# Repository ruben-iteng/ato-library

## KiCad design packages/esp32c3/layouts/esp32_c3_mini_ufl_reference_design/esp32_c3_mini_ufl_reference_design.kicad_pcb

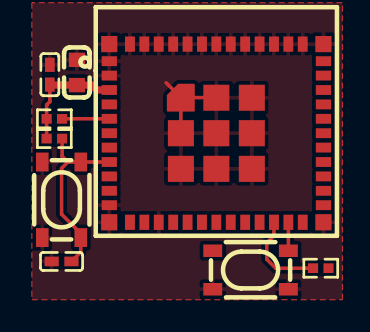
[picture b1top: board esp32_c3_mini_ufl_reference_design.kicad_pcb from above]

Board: 2 copper layers, 9 parts (0 on the bottom side), 6 nets.

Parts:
C1: 22µF ±20% 6.3V X5R; C0603-bd72f6
C2: 100nF ±10% 16V X7R; C0402-b3ef17
C3: 1µF ±10% 25V X5R; C0402-b3ef17
R1, R2, R3: 10kΩ ±1% 62.5mW; R0402-56259e
U1, U3: KEY-SMD_4P-L4.2-W3.2-P2.20-LS4.6
U2: WIFIM-SMD_ESP32-C3-MINI-MINI-1U-1cb675

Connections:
gnd: C1.2, C2.2, C3.2, U1.1, U1.2, U2.1, U2.2, U2.11, U2.14, U2.36, U2.37, U2.38, U2.39, U2.40, U2.41, U2.42, U2.43, U2.44, U2.45, U2.46, U2.47, U2.48, U2.49, U2.50, U2.51, U2.52, U2.53, U2.54, U2.55, U2.56, U2.57, U2.58, U2.59, U2.60, U2.61, U3.1, U3.2
hv: C1.1, C2.1, R1.2, R2.2, R3.1, U2.3
line: R1.1, U2.5
line-1: R2.1, U2.22
output: U1.3, U1.4, U2.23
output-1: C3.1, R3.2, U2.8, U3.3, U3.4

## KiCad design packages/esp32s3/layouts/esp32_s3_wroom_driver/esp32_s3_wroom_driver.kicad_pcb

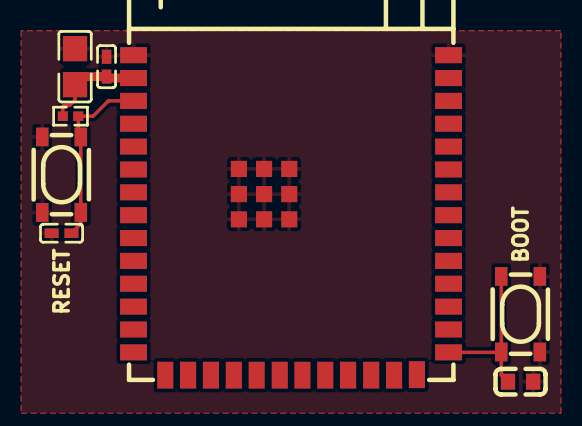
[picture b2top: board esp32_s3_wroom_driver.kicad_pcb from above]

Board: 2 copper layers, 8 parts (0 on the bottom side), 4 nets.

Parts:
C1: 100nF ±10% 50V X7R; C0805
C2, C3: 100nF ±10% 16V X7R; C0402
C4: 100nF ±10% 50V X7R; C0603
R1: 10kΩ ±1% 62.5mW; R0402
U1, U3: KEY-SMD_4P-L4.2-W3.2-P2.20-LS4.6
U2: WIRELM-SMD_ESP32-S3-WROOM-1

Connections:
gnd: C1.2, C2.2, C3.2, C4.2, U1.1, U1.2, U2.1, U2.40, U2.41, U3.3, U3.4
hv: C1.1, C2.1, R1.2, U2.2
line: C3.1, R1.1, U2.3, U3.1, U3.2
line-1: C4.1, U1.3, U1.4, U2.27

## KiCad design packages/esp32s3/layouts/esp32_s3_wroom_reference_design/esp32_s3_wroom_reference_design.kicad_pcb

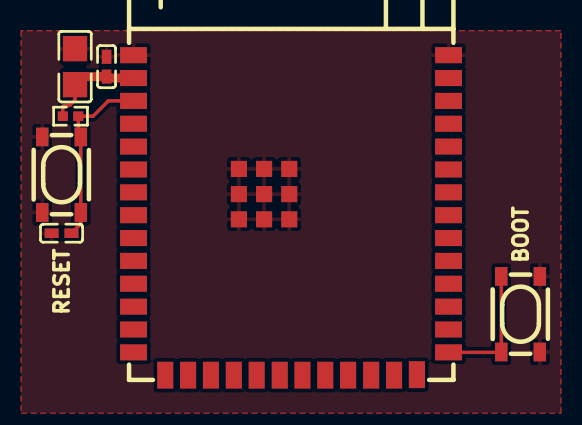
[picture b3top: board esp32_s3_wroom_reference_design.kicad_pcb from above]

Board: 2 copper layers, 7 parts (0 on the bottom side), 4 nets.

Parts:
C1: 100nF ±10% 50V X7R; C0805-3b2e55
C2, C3: 100nF ±10% 16V X7R; C0402-b3ef17
R1: 10kΩ ±1% 62.5mW; R0402-56259e
U1, U3: KEY-SMD_4P-L4.2-W3.2-P2.20-LS4.6
U2: WIRELM-SMD_ESP32-S3-WROOM-1-41522d

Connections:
gnd: C1.2, C2.2, C3.2, U1.1, U1.2, U2.1, U2.40, U2.41, U3.3, U3.4
hv: C1.1, C2.1, R1.1, U2.2
input: C3.1, R1.2, U2.3, U3.1, U3.2
output: U1.3, U1.4, U2.27

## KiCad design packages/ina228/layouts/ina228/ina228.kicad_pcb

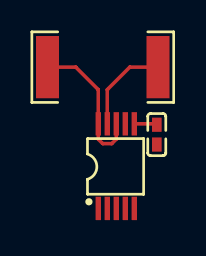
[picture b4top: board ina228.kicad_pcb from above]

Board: 2 copper layers, 3 parts (0 on the bottom side), 4 nets.

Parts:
C1: 100nF ±10% 16V X7R; C0402
R1: 15mΩ ±1% 3W; R2512
U1: VSSOP-10_L3.0-W3.0-P0.50-LS4.9-BL

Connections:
INneg: R1.2, U1.9
INpos: R1.1, U1.8, U1.10
VS: C1.1, U1.6
gnd: C1.2, U1.7

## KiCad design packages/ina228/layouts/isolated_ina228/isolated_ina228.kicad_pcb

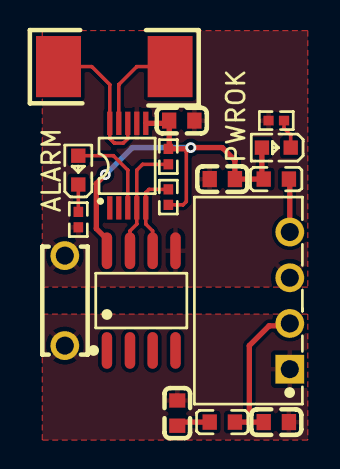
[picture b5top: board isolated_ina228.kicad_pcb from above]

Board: 2 copper layers, 17 parts (0 on the bottom side), 13 nets.

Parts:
C1: 270pF ±10% 2kV; CAP-TH_L6.0-W2.5-P5.00-D1.0-5e41da
C2, C3: 4.7µF ±10% 10V X5R; C0603-bd72f6
C4: 10µF ±10% 10V X5R; C0603-bd72f6
C5: 100nF ±10% 50V X7R; C0603-bd72f6
D1, D2: LED0603-RD-c81ffb
L1, L2: L0603-9cac2b
R1, R3, R4, R5: 1kΩ ±1% 62.5mW; R0402-56259e
R2: 15mΩ ±1% 2W; RES-SMD_L6.4-W3.2-1-4e2b76
U1: SOIC-8_L4.9-W3.9-P1.27-LS6.0-BL-6ccfeb
U2: VSSOP-10_L3.0-W3.0-P0.50-LS4.9-BL-31a551
U3: PWRM-TH_B0505S-1WR3-83f76b

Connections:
alarm_led.led-cathode: D1.1, R1.1
gnd-1: C1.1, C2.2, C3.2, U3.1
gnd-2: C1.2, C4.2, C5.2, R1.2, R3.2, U1.5, U2.7, U3.3
hv: D1.2, U2.3
hv-1: C4.1, C5.1, D2.2, L2.1, R4.2, R5.2, U1.8, U2.6
hv-2: C2.1, L1.1
hv-3: R2.1, U2.8, U2.10
hv-4: R2.2, U2.9
line: R4.1, U1.6, U2.5
line-2: R5.1, U1.7, U2.4
power_indicator-cathode: D2.1, R3.1
power_isolator-hv: L2.2, U3.4
power_isolator-hv-1: C3.1, L1.2, U3.2

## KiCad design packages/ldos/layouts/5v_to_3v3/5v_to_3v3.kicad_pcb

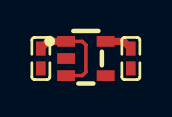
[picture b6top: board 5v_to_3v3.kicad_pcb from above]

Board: 2 copper layers, 3 parts (0 on the bottom side), 3 nets.

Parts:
C1, C2: 100nF ±10% 16V X7R; C0402
U1: SOT-23-5_L2.9-W1.6-P0.95-LS2.8-BR

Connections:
VOUT: C2.1, U1.5
gnd: C1.2, C2.2, U1.2
hv: C1.1, U1.1, U1.3
